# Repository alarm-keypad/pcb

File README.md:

# Alarm keypad PCB

KiCad project for alarm keypad PCB.

You can find a firmware designed to run on this board [on the dedicated repository](https://github.com/alarm-keypad/firmware).

## Required parts

- Resistor for LEDs (value depends on wanted brightness)
- Buzzer (active, 5V, model depends of wanted sound)
- Potentiometer for buzzer (to set sound level)
- Arduino Pro Micro (5V)
- 2x JST connector 1x02 2.50mm pitch (for case mounted LED)
- 2x 2.54mm 8 pins female connectors

## Integration

It is designed to be installed in an aluminium junction box 40x100x110mm.

You can use different kind of keypads, for example:
- Tru Components 4x3, or 4x4 (with A, B, C, D letters),
- Membrane matrix 4x4.

Tru Components 4x3 can be integrated in the case using the following resources.
See [drill and cut file](integration/keypad_drill_cut.pdf) to prepare the case.
Then you can use [this 3D printable border](integration/keypad_border.stl) to
make its integration clean.

## KiCAD project

Arduino Pro Micro KiCAD files can be downloaded
[from this GitHub repository](https://github.com/g200kg/kicad-lib-arduino).

Piher PT-10 potentiometer 3D model can be downloaded
[from grabcad](https://grabcad.com/library/piher-pt-10-1).
Its scale has to be divided by 10.

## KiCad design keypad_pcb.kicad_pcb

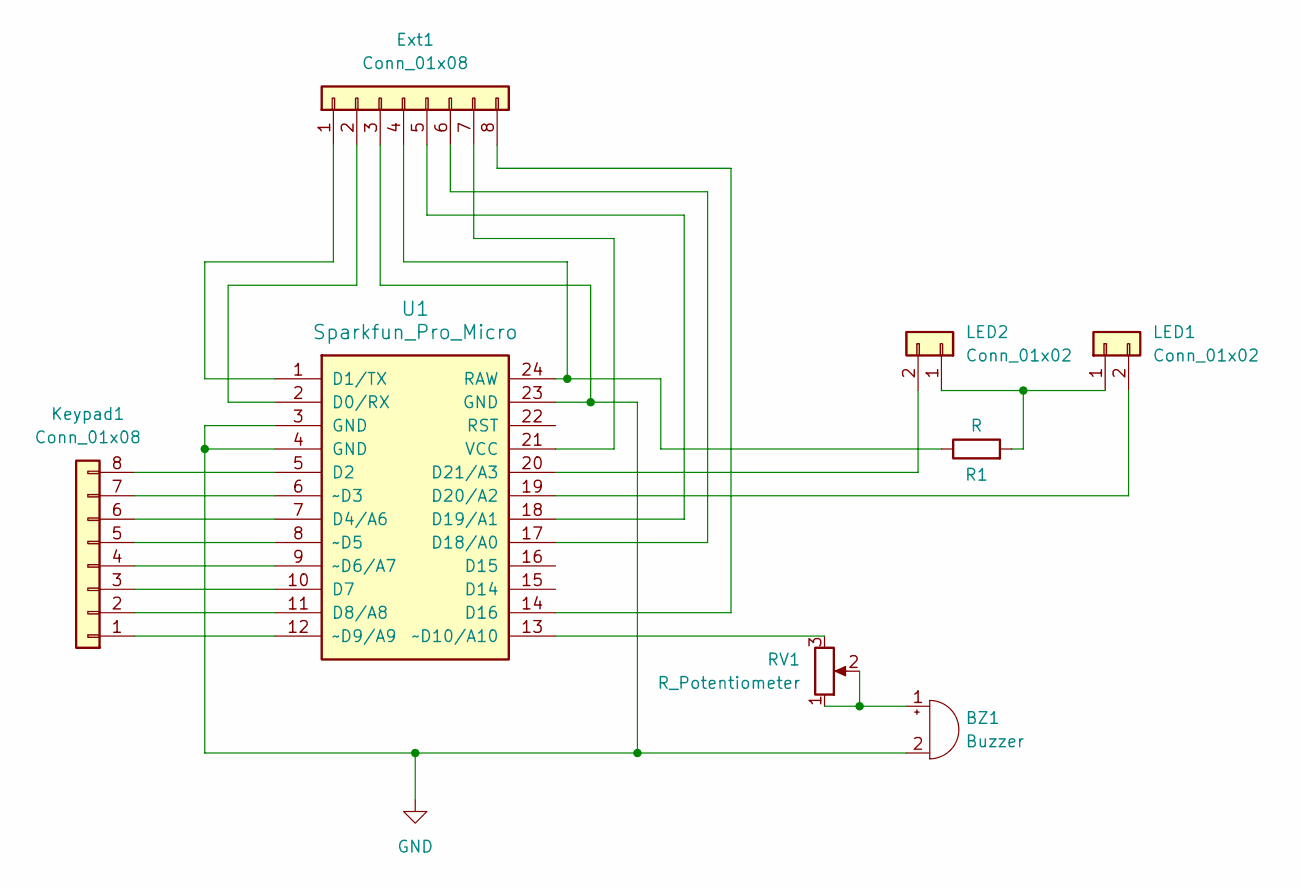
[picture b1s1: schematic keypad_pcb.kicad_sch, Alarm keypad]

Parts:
BZ1: Buzzer; Buzzer_12x9.5RM7.6
Ext1: Conn_01x08; PinHeader_1x08_P2.54mm_Vertical
Keypad1: Conn_01x08; PinHeader_1x08_P2.54mm_Vertical
LED1, LED2: Conn_01x02; JST_XH_B2B-XH-A_1x02_P2.50mm_Vertical
R1: R; R_Axial_DIN0207_L6.3mm_D2.5mm_P10.16mm_Horizontal
RV1: R_Potentiometer; Potentiometer_Piher_PT-10-V10_Vertical_Hole
U1: Sparkfun_Pro_Micro

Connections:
GND: BZ1.2 (+), Ext1.3, U1.3 (GND), U1.4 (GND), U1.23 (GND)
unnamed: BZ1.1 (-), RV1.1, RV1.2
unnamed: Ext1.1, U1.1 (D1/TX)
unnamed: Ext1.2, U1.2 (D0/RX)
unnamed: Ext1.4, R1.1, U1.24 (RAW)
unnamed: Ext1.5, U1.18 (D19/A1)
unnamed: Ext1.6, U1.17 (D18/A0)
unnamed: Ext1.7, U1.21 (VCC)
unnamed: Ext1.8, U1.14 (D16)
unnamed: Keypad1.1, U1.12 (~D9/A9)
unnamed: Keypad1.2, U1.11 (D8/A8)
unnamed: Keypad1.3, U1.10 (D7)
unnamed: Keypad1.4, U1.9 (~D6/A7)
unnamed: Keypad1.5, U1.8 (~D5)
unnamed: Keypad1.6, U1.7 (D4/A6)
unnamed: Keypad1.7, U1.6 (~D3)
unnamed: Keypad1.8, U1.5 (D2)
unnamed: LED1.1, LED2.1, R1.2
unnamed: LED1.2, U1.19 (D20/A2)
unnamed: LED2.2, U1.20 (D21/A3)
unnamed: RV1.3, U1.13 (~D10/A10)

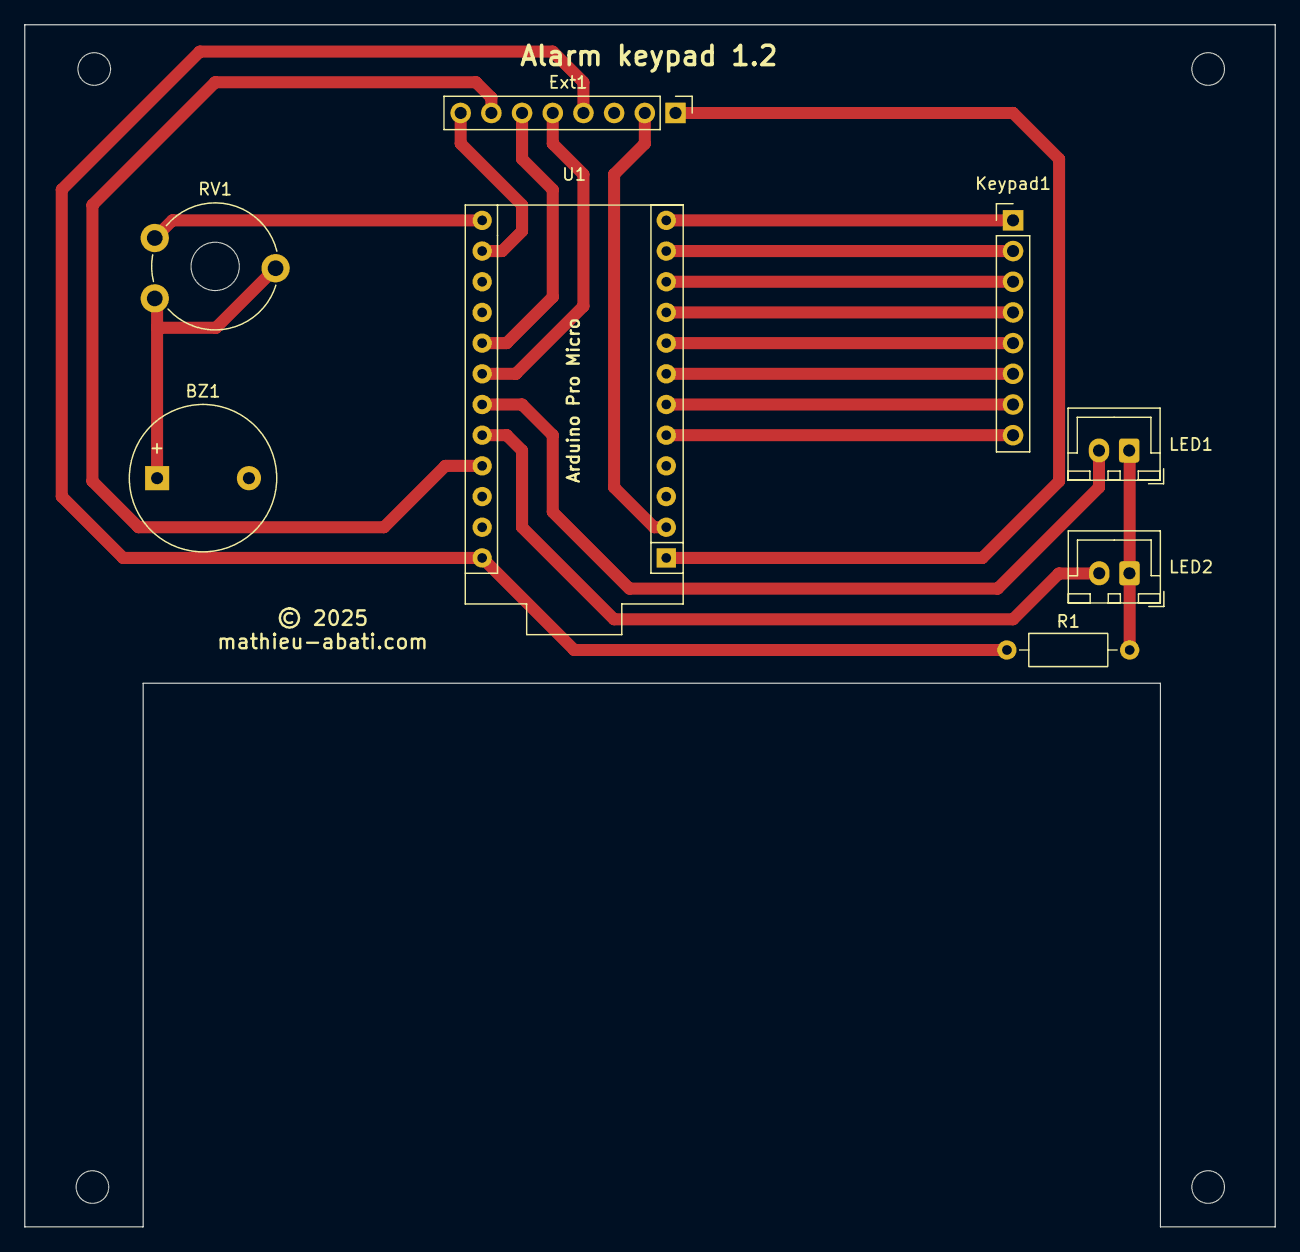
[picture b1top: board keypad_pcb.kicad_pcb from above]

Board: 2 copper layers, 103.5 x 99.5 mm, 9 parts (1 on the bottom side), 21 nets.

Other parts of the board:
G1: LOGO; qr

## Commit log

2025-10-27 First release
2025-10-27 Set version to 1.1
2025-11-15 Rework for Arduino Pro Micro
2025-11-15 Update potentiometer to add PCB hole and integrate 3D shape
2025-11-15 Fixes to be ready to generate gerber
2026-01-30 Update doc and picture
2026-01-30 Set version to 1.2

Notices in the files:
keypad_pcb.kicad_pcb:
© 2025
